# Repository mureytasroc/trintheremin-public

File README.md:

# TrinTheremin (Version 1)
***

---
#### Important Notes -- Read Before Use
* The minimum case material that the board should have when being played or programmed is the top panel.   After you sodder on the sliders use bolts (provided) to secure the top panel (provided for Advanced CS1) onto the board.   Then when you are using the board hold it by the top laser cut panel, not by the board.

* This version (and all versions) are best used with a full case and horn (see the [case folder](Case) and the [horn folder](Horn) ) for ergonomics and sound quality, though the case and horn are not necessary for basic use.

* The circuit will not work properly if the battery is depleted (see [battery section](#battery) below).   If you have been using the same battery for a while or the circuit is acting like it is low on battery (see [battery section](#battery) below), then follow the instructions in the [battery section](#battery) of this readme to measure how much battery is left.   In future versions there will be an onboard battery sensor you can access in your code.

* The board behaves like an Arduino Micro.   See the "Programming" section below.

* When programming the slider to control the volume of the speaker, map your analog reading from 0-1000 to 0-10.   If you use 0-1023 the full volume tones will sound distorted because it will flicker between volume level 9 and 10.

* See the [example code](#example-code-notes) section of this readme on how to conduct the board calibration.

* See the [expanded documentation](#expanded-documentation) for more information on the board as well as expanded procedures and notes.

---
### Expanded Documentation
---
#### About the Circuit
TrinTheremin, like the Sparkfun <a href="https://www.youtube.com/watch?v=2zZkeeQr49g" target="_blank">Digital Sandboxes</a> used in CS1/CS2, is an all in one programmable <a href="https://learn.sparkfun.com/tutorials/what-is-a-circuit" target="_blank">circuit</a> that allows the user to process/control different inputs/outputs on the board.   Its <a href="http://www.atmel.com/Images/Atmel-7766-8-bit-AVR-ATmega16U4-32U4_Datasheet.pdf" target="_blank">ATMEGA microcontroller chip</a> has its own CPU (central processing unit; the brain of the device), flash memory (where your program is stored), SRAM (where the sketch creates and manipulates variables while running), and <a href="http://tronixstuff.com/2011/03/16/tutorial-your-arduinos-inbuilt-eeprom/" target="_blank">EEPROM</a> (NON-VOLATILE storage space programmers can access/use; EEPROM will keep its stored data even without electrical power (when the unit is off), as opposed to volatile memory (like SRAM) that would lose its data without electrical power).   While you probably won't need to use any EEPROM for this project (although feel free to <a href="https://learn.adafruit.com/memories-of-an-arduino/eeprom" target="_blank">do</a> so if you have a use for it), you will constantly be using the CPU and SRAM, as well as the flash memory (where your program lives).   See this chart for how much memory the microcontroller on the TrinTheremin (the ATMEGA 32u4) has of each main type (there are other memory types onboard that I won't go into):

| Memory Type:  | Amount of storage (bytes): |
| ------------- | ------------- |
| Flash  | 32000  |
| SRAM  | 2500  |
| EEPROM  | 1000  |

The flash is not all available, however, as the board's "bootloader" (the software that allows you to upload Arduino code) takes up about 4kB, or 4000 bytes, leaving about 28kB usable for storing code.   The bootloader is already installed on all the boards.

Beyond the chip (and its dedicated hardware such as its crystal and resistors and capacitors), all the circuits on this board should be pretty familiar (with the exception of the speaker's circuit).   See the <a href="https://github.com/TrinitySchoolComputerScience/TrinTheremin/tree/master/Circuit%20Design/Design%20Pictures" target="_blank">circuit design pictures</a> folder.   On the <a href="https://github.com/TrinitySchoolComputerScience/TrinTheremin/tree/master/Circuit%20Design/Design%20Pictures/Schematic/Close%20Ups/Left%20Side%20(Arduino)" target="_blank">left side</a> of the schematic is all the dedicated Arduino hardware, however the <a href="https://github.com/TrinitySchoolComputerScience/TrinTheremin/tree/master/Circuit%20Design/Design%20Pictures/Schematic/Close%20Ups/Right%20Side%20(Peripherals)" target="_blank">right side</a> shows the circuits for all the peripherals (the buttons, switch, light sensor, LEDs, etc).   Take a look at the right side to see how simple (and common) the circuits behind the peripherals are.   The circuit for for the switch, for instance, just includes the switch and a <a href="https://playground.arduino.cc/CommonTopics/PullUpDownResistor" target="_blank">pulldown resistor</a> (which keeps the voltage at 0V unless the switch is closed to 5V) and is connected to a digital pin (D12):

/LowerRight.jpg)

---

#### Usage
The TrinTheremin was purpose built for Trinity's CS2 and Advanced CS1 programs (specifically the physical computing and digital logic units, respectively), although it could be used in a wide variety of applications that use inputs and outputs involving sound and light.

###### Battery
The TrinTheremin's battery should be connected to the 9v battery connector on the bottom of the board and stored in the clip under the slider (also on the bottom of the board).  

Like any device, the TrinTheremin will eventually run out of battery.   Trinity's collection of Apex batteries have a 595mAh capacity.   Milliamp hours (mAh) are a unit of electrical charge (one milliamp hour is about 3.6 coulombs, a unit commonly taught in Trinity physics that is generally used when working with static electricity rather than circuits).   This means that the batteries can supply 595 mA of current for one hour. The TrinTheremin draws about 400 mA when the speaker is on at full volume so at minimum the TrinTheremin will run for about 1.5 hours (with everything running and its speaker on at full volume) continuously.   If you do not have the speaker on the device draws only about 25 mA, which will yield about a day of continuous use (so do not feel the need to turn off the device while programming it as having it on does not use up much battery life) To more accurately determine how much battery life the device has left (and without keeping track of how much time you have used it for), you can measure the remaining battery life with a multimeter (located in the top drawer in the drawers by the door in the computer science lab -- ask Mr. Rose or Mr. Gohde if you are unsure where this is) and a few quick calculations.

First, set the multimeter to measure DC voltage and make sure the leads are connected to the right ports (red to positive (+) and black to negative (-, sometimes referred to as COM) -- see this <a href="https://learn.sparkfun.com/tutorials/how-to-use-a-multimeter" target="_blank">tutorial on multimeters</a>.   Then measure the voltage of the battery (touching the red lead of the multimeter to the positive terminal of the battery (marked by the + symbol on the battery) and the black lead to the negative terminal (marked by the -).   Here is a chart that shows the battery life estimates for an alkaline cell:

| Alkaline Voltage Level and Range (V):  | Usability: |
| ------------- | ------------- |
| 1.50  | New and unused  |
| 1.35 – 1.49  | Good  |
| 1.20 – 1.34  | Average  |
| 1.10 – 1.19  | Low  |
| 0.90 – 1.09  | Very Low  |
| < 0.90  | Dead – Discard!  |

Given that alkaline 9v batteries (Trinity's Apex 9v batteries are alkaline) are 6 alkaline cells, we can multiply through these ranges to find voltages that apply to the reading from the 9v battery:

| 9v Battery Voltage Level and Range (V):  | Usability: |
| ------------- | ------------- |
| 9  | New and unused  |
| 8.1 – 8.94  | Good  |
| 7.2 – 8.04  | Average  |
| 6.6 – 7.14  | Low (Unusuable below about 6.75v)|
| 5.4 – 6.54  | Very Low (Unusable)|
| < 5.4  | Dead – Discard! (Unusable)|

There is one more factor to consider, though, and that is that the TrinTheremin needs about 6.75v to run properly.   This is because the voltage regulator (a chip on the board that takes the voltage being supplied by the battery and regulates it at a constant 5v for the circuit to use) needs at least 6.75v to be able to output 5v as its supposed to.   This extra 1.75 volts it needs is called the "dropout voltage" -- this chart from the chip's <a href="http://www.st.com/content/ccc/resource/technical/document/datasheet/41/4f/b3/b0/12/d4/47/88/CD00000444.pdf/files/CD00000444.pdf/jcr:content/translations/en.CD00000444.pdf" target="_blank">datasheet</a> was how I found that the dropout voltage is 1.75 volts (assuming 25C temperature and 500mA current draw):

If the board is acting weird or blatantly executing programming commands incorrectly (that's not because of mistakes in the code) it is almost certainly because its does not have the necessary voltage (so measure it and replace the battery if necessary). There is a small range of voltages where the board will turn on but may work improperly.   

###### Programming
The TrinTheremin has the same chip as an <a href="https://store.arduino.cc/usa/arduino-micro">Arduino Micro</a>, so it will behave almost identically to that board.   Important caveats to note:
* When using Serial (rx/tx) on the "COM breakout" you must use Serial1 instead of Serial.   Since this chip has its own embedded usb circuit, Serial.print will print to the Arduino console as usual, however Serial1 will reference the hardware serial ports (rx/tx). So you would use Serial1.begin(9600), Serial1.print("text"), etc to use the HARDWARE serial.   On an Arduino Uno, for example, which has an external USB circuit that is connected inline with the hardware serial ports, the Serial command references both the hardware and the usb serial (so Serial.print will output serial on the tx port but also print to the Arduino developer's console)

* Because the chip has built in USB, when you plug it into your computer it will be recognized as a mouse or keyboard (and you can actually use it as such -- more on that <a href="https://www.arduino.cc/en/Reference/MouseKeyboard">here</a>).

* When you upload your code, select "Arduino Micro" under boards, and the appropriate port under ports.

-----

###### Example Code Notes

* When programming the slider to control the volume of the speaker, map your analog reading from 0-1000 to 0-10.   If you use 0-1023 the full volume tones will sound distorted because it will flicker between volume level 9 and 10.

* The calibration procedure in the example code is this: 
  i. When one LED is blinking do not cover the sensor at all -- it is measuring the ambient light levels; 
  ii. Once the speaker makes a noise and the LED stops blinking cover the sensor with your hand
  iii. Once both LEDs stop blinking and then light up in a pattern the calibration process is complete

* The autoplay feature can work very well if you put your hand over the dancing LED and the sensor.   It will work fine if you leave it in ambient light, but the more ambient light there is, the worse it will work (this cannot be fixed in calibration -- think about it like the LED's light is getting drowned out).

* The toneAc library is used to control the speaker.   To download toneAc see this <a href="https://bitbucket.org/teckel12/arduino-toneac/wiki/Home">link</a>.   Here is the toneAc <a href="https://playground.arduino.cc/Code/ToneAC">reference</a>.

-------
#### Plans for future versions
If any future versions of the TrinTheremin are produced these are some of the goals that did not get included in this initial version:

* _A more efficient amplifier_ -- the amplifier circuit on the TrinTheremin right now is very simple to use and understand (both in software and in hardware), works with the ToneAC library, and has pretty good quality sound (meeting the goals of the board).   However in future versions a more sophisticated amplifier circuit might be combined with a possible TrinTheremin Arduino library to keep the software simplicity of ToneAC while improving quality and GREATLY improving efficiency (battery life would be improved immensely).

* _A voltage divider circuit_ -- this is one of the easiest (and also most helpful) changes that could be introduced in future versions.   Essentially this would take the voltage of the battery, divide it in two (9v becomes 4.5, 7 becomes 3.5, etc), and feed it to an analog input (0v-5v yields a 0-1023 reading) on the microcontroller.   This would allow the programmer to measure the voltage of the battery.   With this they could create an integrated battery life check that would alert the user if the battery were low.

* _Headphone jack_ -- a headphone jack could be added to the board in addition to the speaker so the user could play with headphones on.   The port would have a switch in it that would be conencted to a digital pin so the programmer could automatically turn off the speaker when headphones are plugged in.

* _Reduced cost_ -- right now the TrinTheremin costs about 25$ per board to produce, however with hardware changes and different production methods, this could potentially be significantly reduced.   For reference an Arduino Micro costs about 22$ (with no inputs or outputs built in)

* _Expanded documentation and a more seamless user interface -- maybe a website?_ -- Right now trintherem.in redirects to this github repository, however in the future a website dedicated to the TrinTheremin could be produced.

----

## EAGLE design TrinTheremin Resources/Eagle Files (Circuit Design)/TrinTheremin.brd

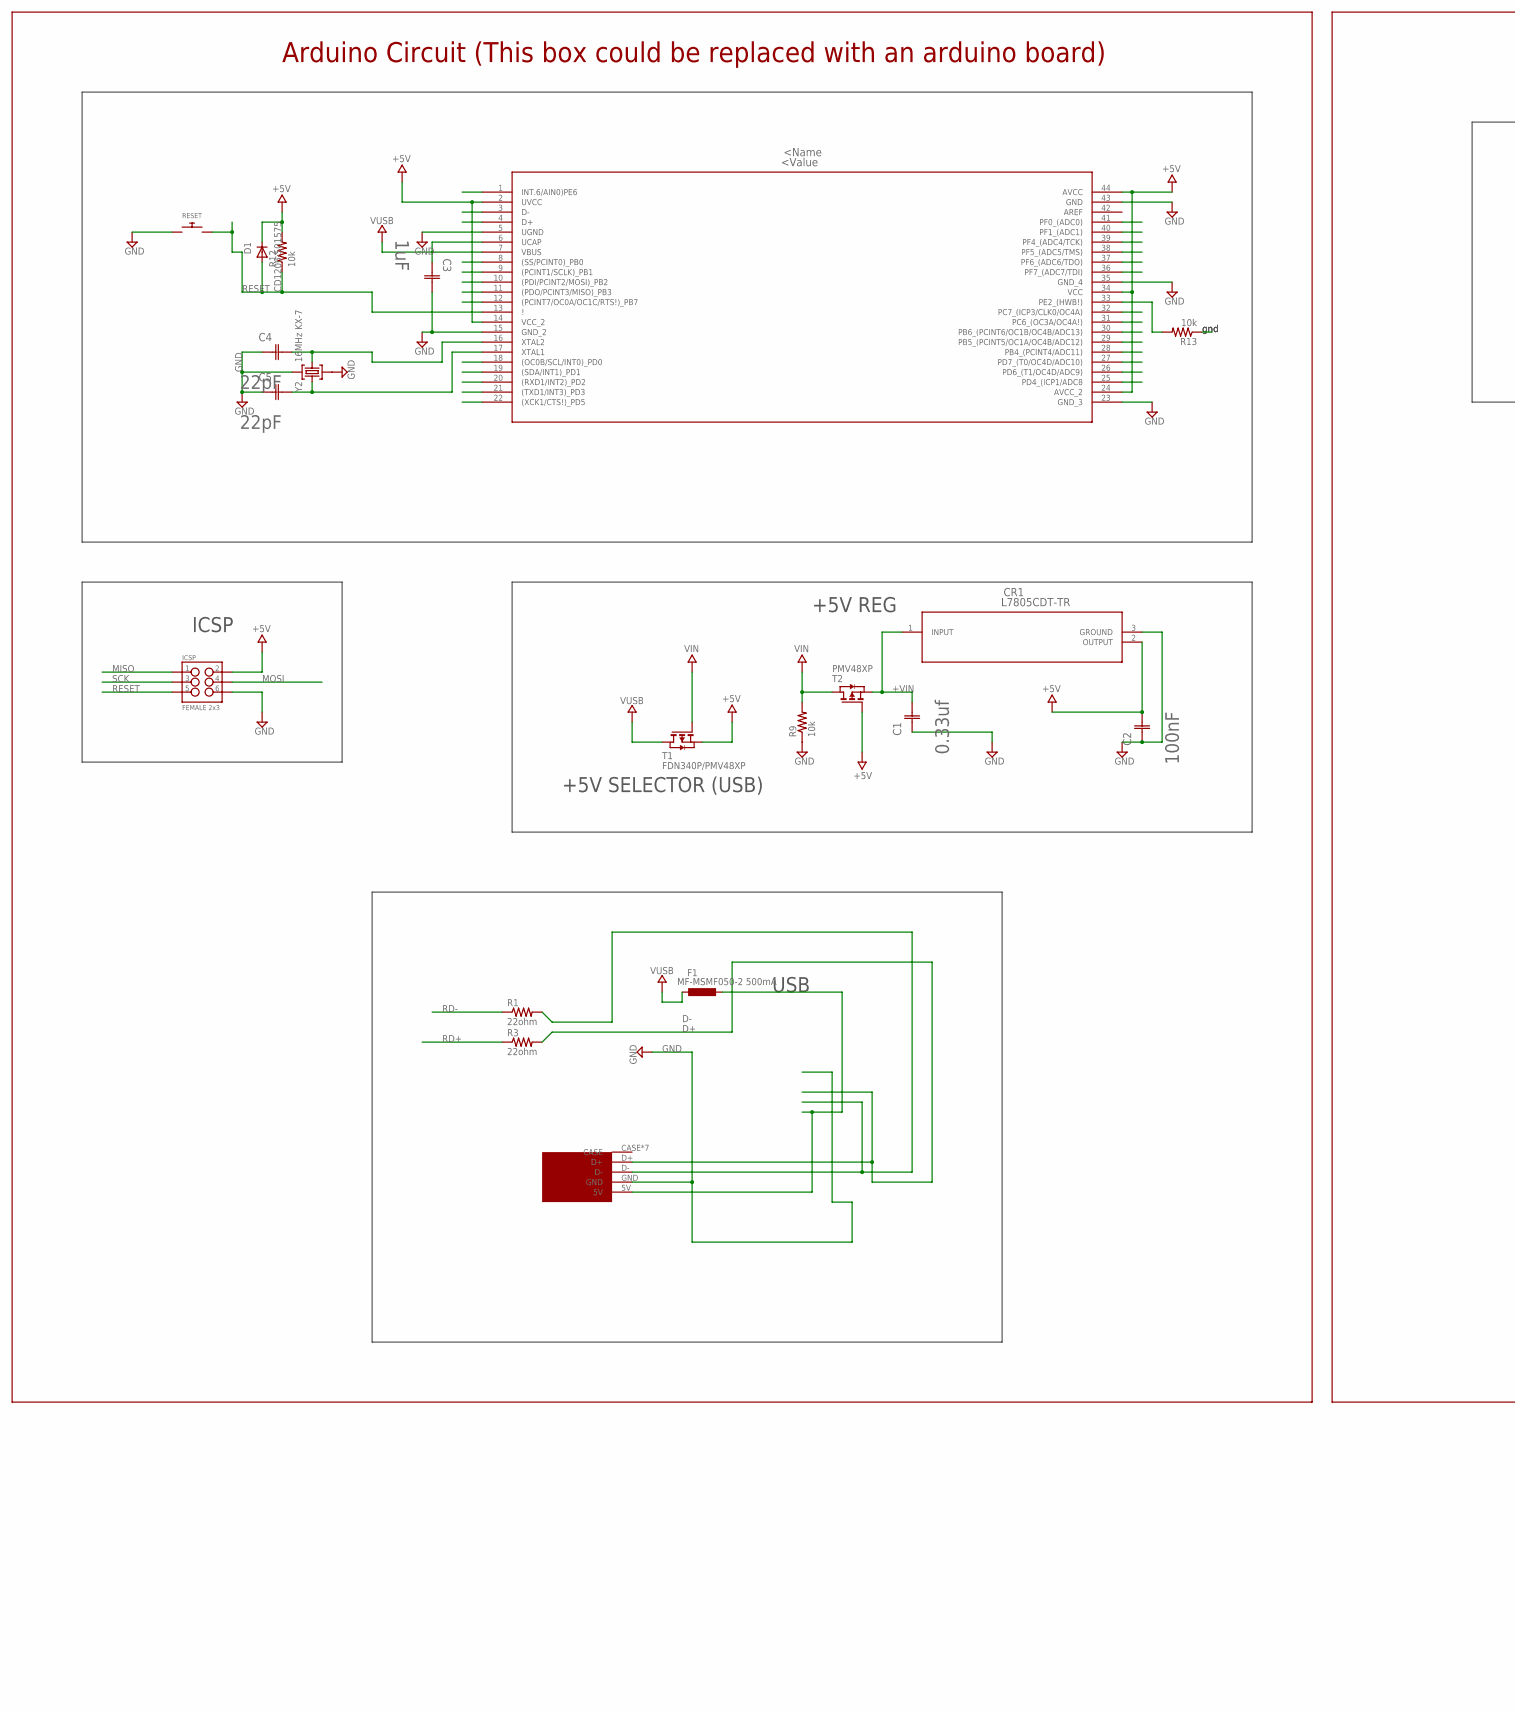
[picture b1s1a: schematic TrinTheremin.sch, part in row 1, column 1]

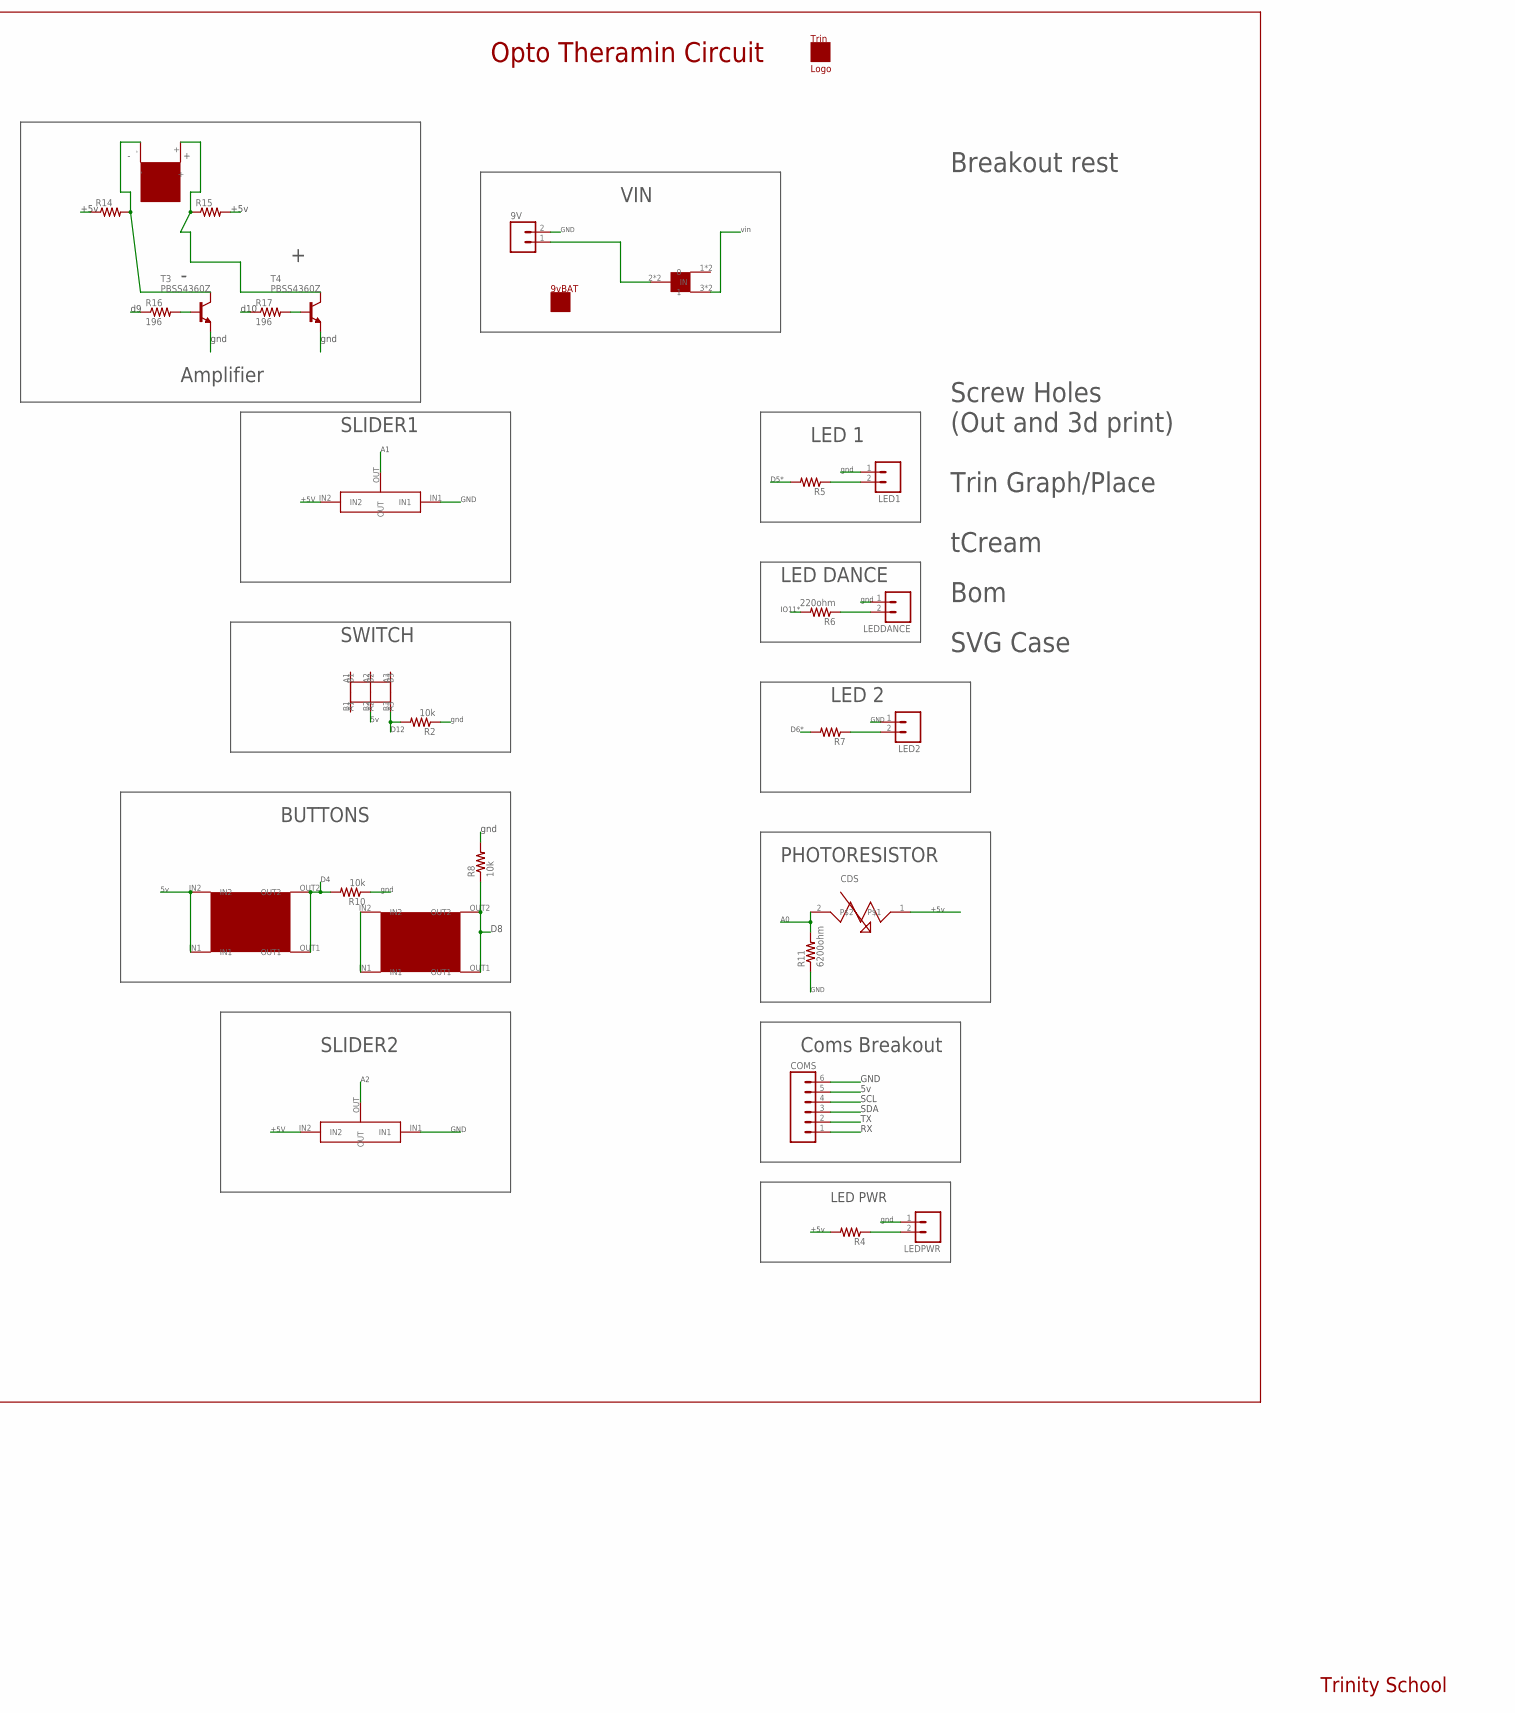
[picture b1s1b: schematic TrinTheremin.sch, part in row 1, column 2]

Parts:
9V: M02PTH; 1X02
C1: 0.33uf; CAPC2013X110N
C2: 100nF; CAPC2013X110N
C3: 1uF; CAPC1608X85N
C4, C5: 22pF; CAPC1608X85N
COMS: M06SILK_FEMALE_PTH; 1X06
CR1: L7805CDT-TR; DPAK
D1: CD1206-S01575; MINIMELF
F1: MF-MSMF050-2 500mA; L1812
ICSP: FEMALE 2x3; 2X3
LED1, LED2: M02PTH; 1X02
LEDDANCE: M02PTH; 1X02
LEDPWR: M02PTH; 1X02
R1, R3: 22ohm; R0603
R2, R8, R9, R10, R12, R13: 10k; 0603-RES
R4, R5, R7: RESISTOR0603; 0603-RES
R6: 220ohm; 0603-RES
R11: 6200ohm; 0603-RES
R14, R15: R-US_R2512; R2512
R16, R17: 196; 1206
RESET: SWITCH_PUSHBUTTONC&K_KSS; BTN_CK_KSS
T1: FDN340P/PMV48XP; SOT-23
T2: PMV48XP; SOT-23
T3, T4: PBSS4360Z; SOT223
U$3: ATMEGA32U4-AU; 44ML
U$8: PWRSWITCHTHRU
U$9: CDS
U$10, U$14: DIGISLIDER
U$11: DIGISWITCH
U$13, U$17: BUT97
U$15: 9VBATHOLDERTALL
U$16: TRIN
U$20: GOODSPEAKER
U$23: MICROUSB
Y2: 16MHz KX-7; CRYSTAL-3.2-2.5

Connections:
+5V: C2.2 (C2), COMS.5, CR1.2 (OUTPUT), D1.C, ICSP.2, R4.2, R12.2, R14.1, R15.2, T1.2 (S), T2.3 (G), U$3.2 (UVCC), U$3.14 (VCC_2), U$3.24 (AVCC_2), U$3.34 (VCC), U$3.44 (AVCC), U$9.1, U$10.IN2, U$11.B2, U$13.IN1, U$13.IN2, U$14.IN2, U$17.IN1, U$17.IN2
+VIN: C1.2 (C2), CR1.1 (INPUT), T2.2 (S)
A0: R11.2, U$3.36 (PF7_(ADC7/TDI)), U$9.2
A1: U$3.37 (PF6_(ADC6/TDO)), U$10.OUT
A2: U$3.38 (PF5_(ADC5/TMS)), U$14.OUT
A3: U$3.39 (PF4_(ADC4/TCK))
A4: U$3.40 (PF1_(ADC1))
A5: U$3.41 (PF0_(ADC0))
BASE: R16.2, T3.1 (B)
COL: R14.2, T3.2 (C), T3.4 (C), U$20.-
D0/RX: COMS.1, U$3.20 ((RXD1/INT2)_PD2)
D1/TX: COMS.2, U$3.21 ((TXD1/INT3)_PD3)
D2/SDA: COMS.3, U$3.19 ((SDA/INT1)_PD1)
D3/SCL: COMS.4, U$3.18 ((OC0B/SCL/INT0)_PD0)
D4*: R10.2, U$3.25 (PD4_(ICP1/ADC8), U$13.OUT1, U$13.OUT2
D5*: R5.2, U$3.31 (PC6_(OC3A/OC4A!))
D6*: R7.2, U$3.27 (PD7_(T0/OC4D/ADC10))
D7: U$3.1 (INT.6/AIN0)PE6)
D+: R3.2, U$23.D+
D-: R1.2, U$23.D-
GND: 9V.2, C1.1 (C1), C2.1 (C1), C3.2 (C2), C4.1 (C1), C5.1 (C1), COMS.6, CR1.3 (GROUND), ICSP.6, LED1.1, LED2.1, LEDDANCE.1, LEDPWR.1, R2.1, R8.2, R9.1, R10.1, R11.1, R13.1, RESET.P$1, T3.3 (E), T4.3 (E), U$3.5 (UGND), U$3.15 (GND_2), U$3.23 (GND_3), U$3.35 (GND_4), U$3.43 (GND), U$10.IN1, U$14.IN1, U$23.GND, Y2.2 (GND), Y2.4 (GND)
HWB: R13.2, U$3.33 (PE2_(HWB!))
IO8: R8.1, U$3.28 (PB4_(PCINT4/ADC11)), U$17.OUT1, U$17.OUT2
IO9*: R16.1, U$3.29 (PB5_(PCINT5/OC1A/OC4B/ADC12))
IO10*: R17.1, U$3.30 (PB6_(PCINT6/OC1B/OC4B/ADC13))
IO11*: R6.2, U$3.12 ((PCINT7/OC0A/OC1C/RTS!)_PB7)
IO12*: R2.2, U$3.26 (PD6_(T1/OC4D/ADC9)), U$11.B3
IO13*: U$3.32 (PC7_(ICP3/CLK0/OC4A))
MISO: ICSP.1, U$3.11 ((PDO/PCINT3/MISO)_PB3)
MOSI: ICSP.4, U$3.10 ((PDI/PCINT2/MOSI)_PB2)
unnamed: LED1.2, R5.1
unnamed: R17.2, T4.1 (B)
unnamed: C3.1 (C1), U$3.6 (UCAP)
unnamed: R15.1, T4.2 (C), T4.4 (C), U$20.+
unnamed: LEDDANCE.2, R6.1
unnamed: LED2.2, R7.1
unnamed: 9V.1, U$8.2 (IN), U$8.5 (IN)
unnamed: LEDPWR.2, R4.1
RAWUSB: F1.1, U$23.5V
RD+: R3.1, U$3.4 (D+)
RD-: R1.1, U$3.3 (D-)
RESET: D1.A, ICSP.5, R12.1, RESET.P$2, U$3.13 (!)
RXLED/SS: U$3.8 ((SS/PCINT0)_PB0)
SCK: ICSP.3, U$3.9 ((PCINT1/SCLK)_PB1)
TXLED: U$3.22 ((XCK1/CTS!)_PD5)
VIN: R9.2, T1.3 (G), T2.1 (D), U$8.3 (1), U$8.6 (1)
VUSB: F1.2, T1.1 (D), U$3.7 (VBUS)
XTAL3: C4.2 (C2), U$3.16 (XTAL2), Y2.1 (C1)
XTAL4: C5.2 (C2), U$3.17 (XTAL1), Y2.3 (C2)

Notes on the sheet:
+5V REG
ICSP
USB
+5V SELECTOR (USB)
CDS
GND
gnd
Arduino Circuit (This box could be replaced with an arduino board)
Opto Theramin Circuit
Trinity School
LED 2
LED DANCE
Coms Breakout
PHOTORESISTOR
LED 1
+5v
VIN
SWITCH
BUTTONS
SLIDER1
SLIDER2
vin
+5V
LED PWR
D5*
D6*
IO11*
D12
Breakout rest
Screw Holes (Out and 3d print)
Trin Graph/Place
tCream
Bom
SVG Case
Amplifier
d10
SDA
SCL

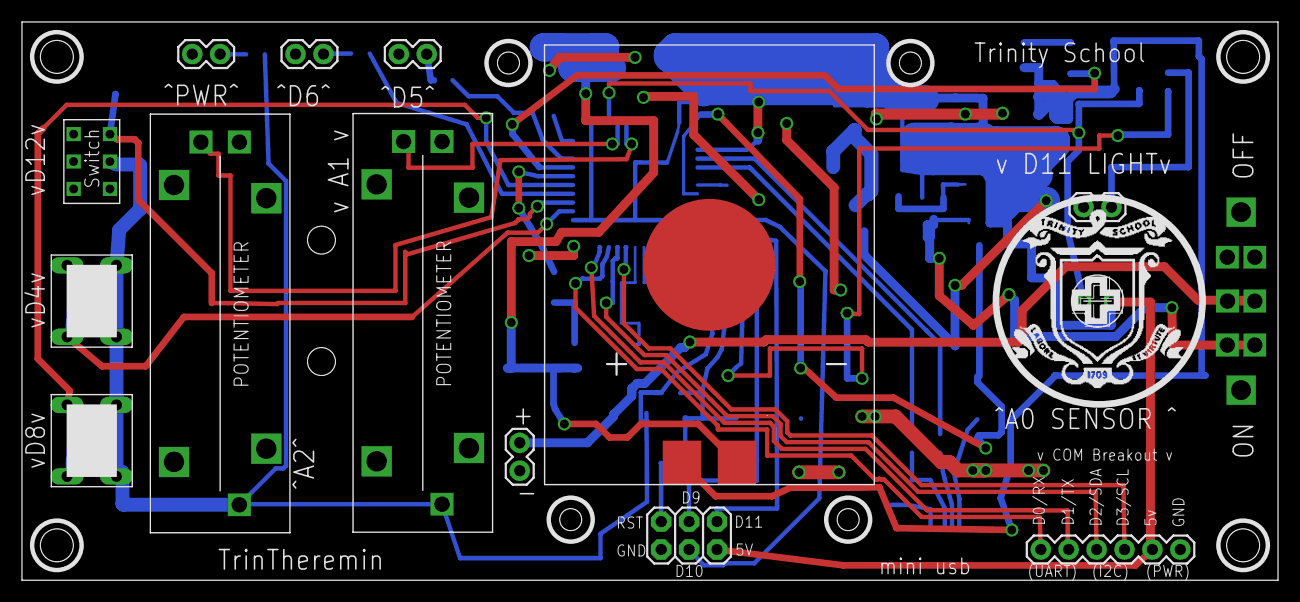
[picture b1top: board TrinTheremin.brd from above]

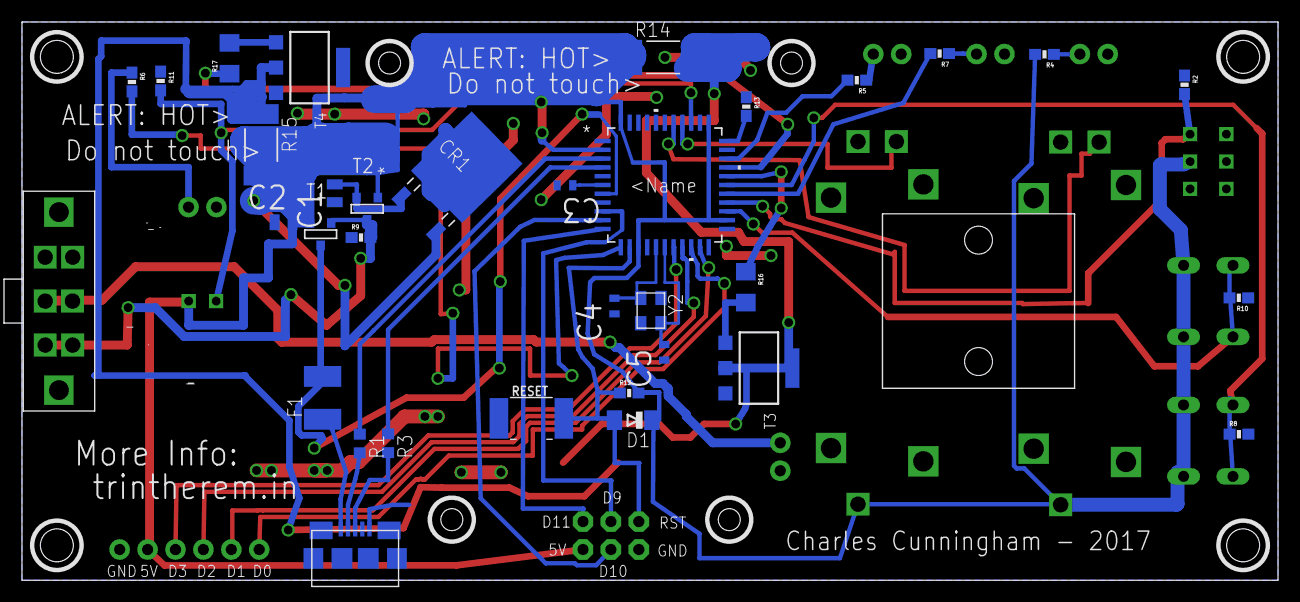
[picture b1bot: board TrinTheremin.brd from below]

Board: 2 copper layers, 114.3 x 50.8 mm, 50 parts (35 on the bottom side), 42 nets.

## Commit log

2017-09-11 Added design files... literature in development.
    To do: datasheet, readme, possibly different 3d design formats?
2017-09-11 Unnecessary file
2017-09-11 Added missing files
2017-09-11 Renamed Folders
2017-09-12 Misc. Changes... see details
    Added circuit design pictures, fixed horn (reversed), changed solidworks
    files to display PCB below part, added datasheet (in progress), changed
    folder names, reorganized
2017-09-12 Added folder organization
2017-09-13 Added Readme figures folder
2017-09-13 Folder Organization
2017-09-14 Added Code
2017-09-14 Reorganized example code
2017-12-03 Added Horn MK2
2017-12-03 Changed Horn
2017-12-04 Changed Example Code
2017-12-04 Example Code Updated
2017-12-04 Added User Manual
2017-12-04 Updated Manual
2017-12-20 Changes to user manual
2017-12-20 Example Code Changes
2017-12-20 Fixed Autoplay Feature
2017-12-21 Changed folder names and consolidated example codes
2018-10-09 Moved Manual Into Folder

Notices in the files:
parts and their libraries:
SparkFun-Connectors: Licensing: Creative Commons ShareAlike 4.0 International - https://creativecommons.org/licenses/by-sa/4.0
NXP_60_26022015: This library may be distributed and adapted freely for any purpose, as long as NXP is credited and any new creation is licensed under the same terms.
